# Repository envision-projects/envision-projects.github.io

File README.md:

# [envision-projects.github.io](https://envision-projects.github.io)
Project and certification website for the EnVision makerspace, for use by EnVision administration

## Content Management System

This is the quickest and simplest option for writing and setting up a page. Navigate to [envision-projects.github.io/admin](https://envision-projects.github.io/admin) and sign in with your GitHub account. If prompted, you must give Netlify CMS permission to author commits and push on your behalf. 

After signing in, you can access the different sections of the website and view media that has been uploaded. The CMS is pretty self explanatory.

- Everything is organized into pre-defined sections; there is unfortunately not _yet_ support for nested folders. 
- Files titled `_index.md` are top level files; for example, when you click on **Mechanical** on the website, it takes you to the `_index.md` file for the mechanical section. 
- In the editor, you can either edit in WYSIWYG _"Rich Text"_ mode, or you can edit the markdown directly. 
- The preview on the right gives a basic preview of how the website will look.
- In the rich text editor, you can add links, headings, quotes, code blocks, and other elements (found under the `+` tab.)
  - For images, use the `image` element and please upload your image to the website by clicking `choose an image > upload`
  - `Tip` and `Warning` elements make your article more readable and highlight important information
  - When creating a link, use either the absolute location of the page or the relative location. For example, to link to `envision-projects.github.io/mechanical/3d-printing` the text of my link would read `/mechanical/3d-printing`. Otherwise, `3d-printing` if the file I was editing was in the same folder as the the file I was linking

When editing the page is complete, make sure that you have a title and a description (the publish date may be left as is, or set to the current time by clicking `now`). This will author a git commit with your changes and start the process of the page getting published, which should take around 5 minutes or so.

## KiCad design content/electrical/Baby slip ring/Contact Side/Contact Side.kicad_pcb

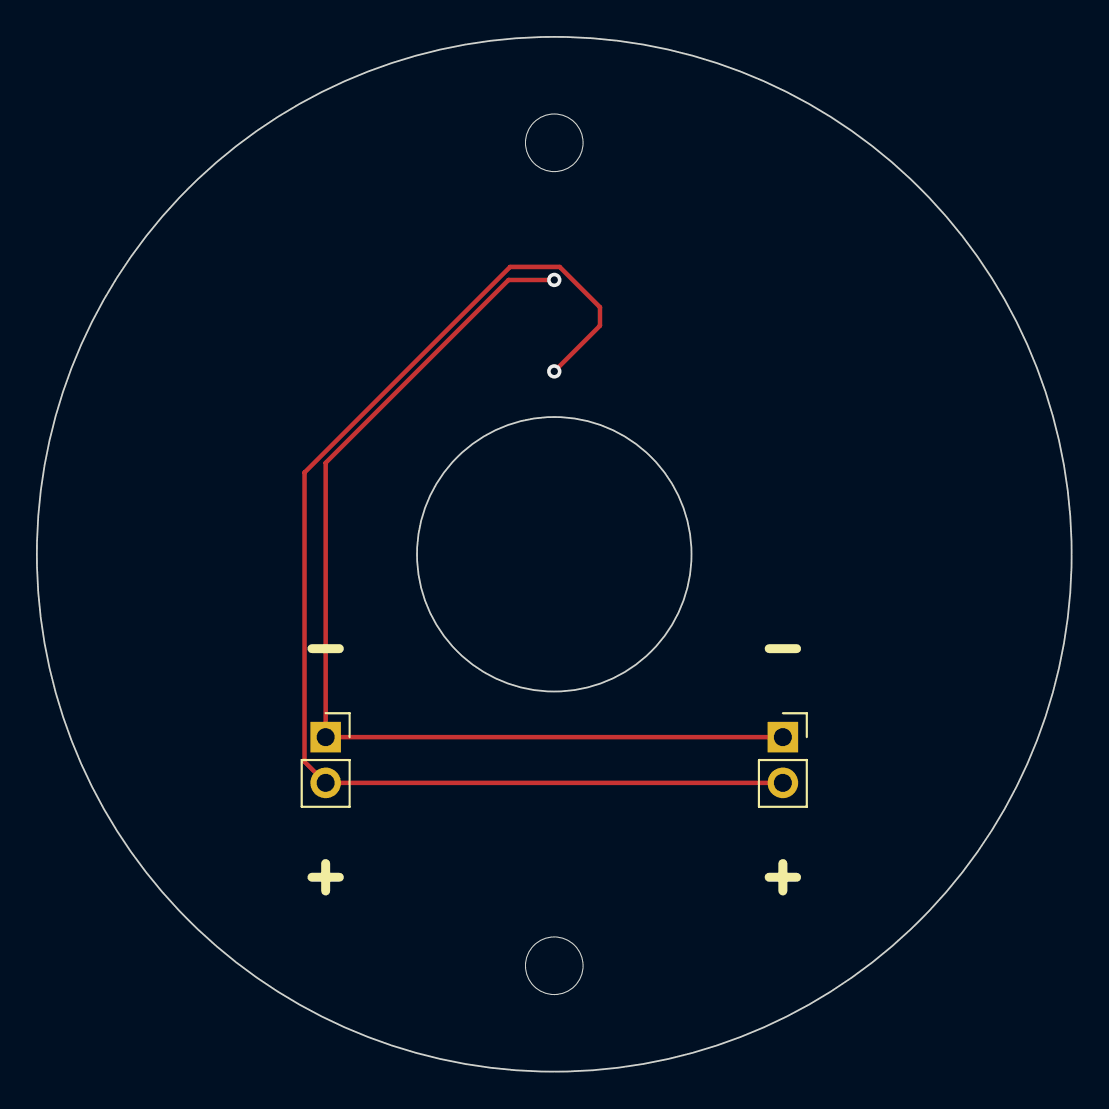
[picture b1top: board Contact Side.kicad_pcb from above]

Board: 2 copper layers, 57.5 x 57.5 mm, 3 parts (0 on the bottom side), 2 nets.

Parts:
D1, D2: LED; PinSocket_1x02_P2.54mm_Vertical
U1: 2_Wire_contact; Contact Pads

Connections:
unnamed: D1.1 (K), D2.1 (K), U1.2 (GND)
unnamed: D1.2 (A), D2.2 (A), U1.1 (+)

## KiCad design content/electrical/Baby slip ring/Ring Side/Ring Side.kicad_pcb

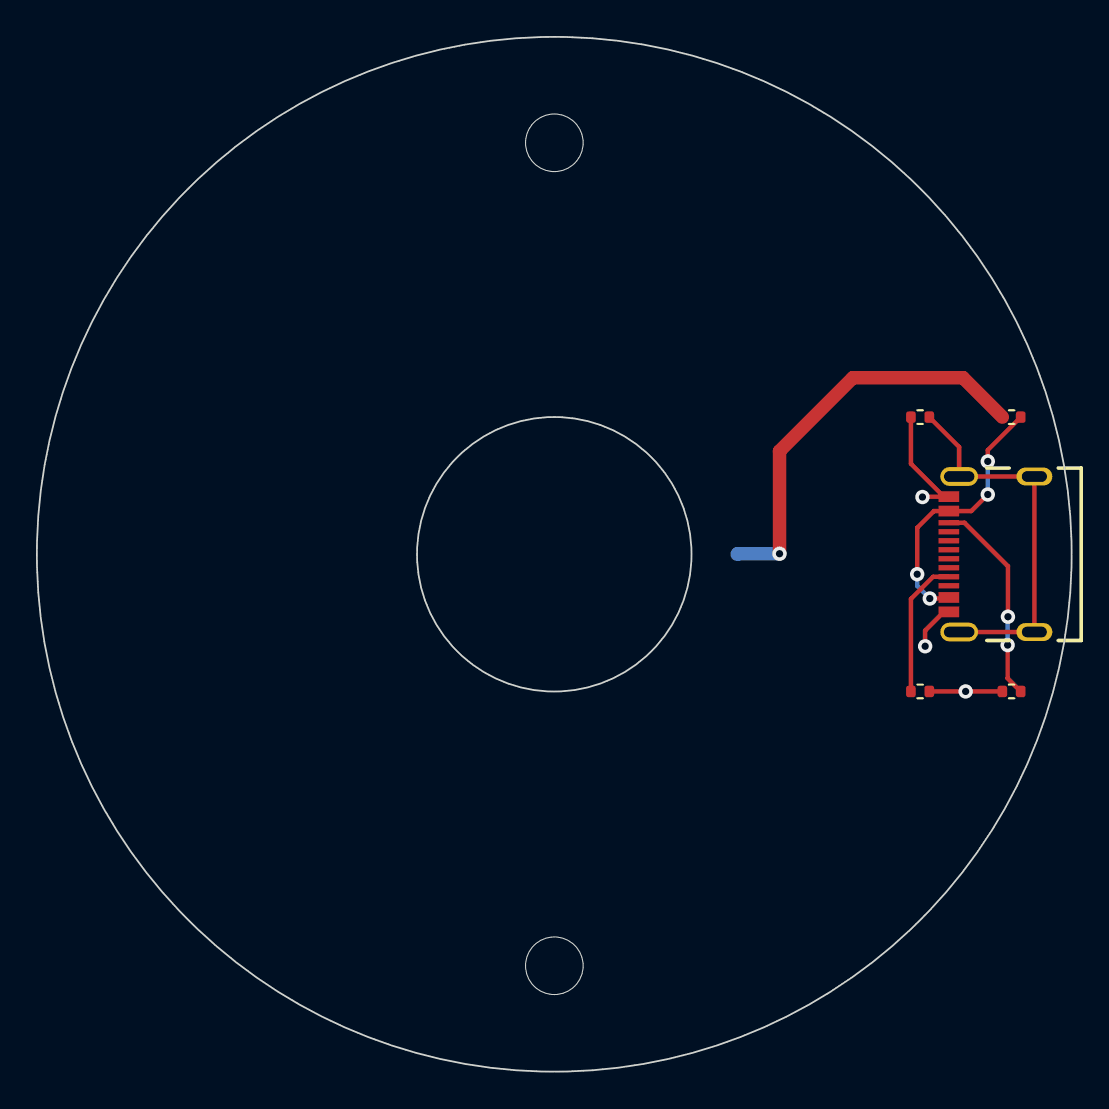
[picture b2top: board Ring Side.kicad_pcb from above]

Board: 2 copper layers, 57.5 x 57.5 mm, 6 parts (0 on the bottom side), 6 nets.

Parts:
J1: USB4105-GF-A; GCT_USB4105-GF-A
R1, R2, R3: 5.1k; R_0402_1005Metric
R4: 470; R_0402_1005Metric
U1: 2_Wire_Ring; 2 Wire Ring

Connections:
GND: J1.A1_B12 (GND), J1.B1_A12 (GND), R1.1, R2.2, R3.2, U1.2 (GND)
unnamed: J1.A5 (CC1), R2.1
unnamed: J1.B5 (CC2), R3.1
unnamed: J1.S1 (SHELL_GND), J1.S2 (SHELL_GND), J1.S3 (SHELL_GND), J1.S4 (SHELL_GND), R1.2
unnamed: R4.1, U1.1 (+)
VCC: J1.A4_B9 (VBUS), J1.B4_A9 (VBUS), R4.2

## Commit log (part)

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2022-08-20 Upload “static/images/ss_arduino3.png”
2022-08-20 Upload “static/images/ss_arduino4.png”
2022-08-20 deploy: 2372934986aabecab25a083c6f30b87d16d41531
2022-08-20 deploy: ffc908f2f898e9946a42e9ee863fea94732f23bf
2022-08-20 Update Embedded Doc “simplesynth-project”
2022-08-20 deploy: 133ec2f00fa13bb67a5334d09d234f5a2b53127c
2022-08-20 deploy: 40410a8e25bdb81d0f237bd15896728e04bf8dff
2022-08-20 deploy: 8ceef5e628713276af94d59dcca4fada12961cde
2022-08-20 deploy: 50fd72f3267697be6b3bff215566b59305df6ea2
2022-08-20 deploy: 155d112f24f32613291aa5aaef3b2dea806dec3c
2022-08-20 Upload “static/images/ss_arduino5.png”
2022-08-20 deploy: 29a4fec32ebb02036e70014a1d3cc810db219dc3
2022-08-21 deploy: b7fe7fb9bde3a6ba3234f25e762e081013418df0
2022-08-21 deploy: 04b6dcef45a325cac162a2d89fcd979c88191e97
2022-08-21 deploy: 1d4640db6f8ef7461e3dbfcc6b8ed846a95634ac
2022-08-21 deploy: 3e80fe1010d79a2bc296ffe44b24c91c7f3f80b6
2022-08-21 Upload “static/images/ss_arduino6.png”
2022-08-21 deploy: e3aaaaf135ae04b4449748d5dd0e17e8b8a83cf4
2022-08-21 deploy: ea1c58187608d7010fc90b4f36d01908c555f3cf
2022-08-21 deploy: e2c86d121907457488cf06fd51179e16c65fa246
2022-08-21 Upload “static/images/ss_arduino7.png”
2022-08-21 Upload “static/images/ss_arduino8.png”
2022-08-21 Upload “static/images/ss_arduino9.png”
2022-08-21 deploy: 536dd113ab888d18e6fb7fc49f578e0ecc064b4a
2022-08-21 deploy: ddb818c62ab50bc87a0f1c0744fa16b6ff034ac3
2022-08-21 deploy: 63f21a9aa49874f6ecfaf76b174b1cf13b130a9e
2022-08-21 deploy: 64e6962d8ffcb7b05a55ab547d92bc5ad229678c
2022-08-21 deploy: 253067c8290102d94707a06eb677e59a7d906e8b
2022-08-21 deploy: fb1c90918f9881cf0ca3361f134dafda739fe788
2022-08-21 Upload “static/images/ss_asd7.png”
2022-08-21 Upload “static/images/ss_asd4.png”
2022-08-21 Upload “static/images/ss_asd5.png”
2022-08-21 deploy: e3cb9491196d23922fbf4fa6283915c229c482e1
2022-08-23 Update Electrical Doc “_index”
2022-08-23 deploy: 5b276313f6897d91253888ef9ddf6fb67e22ab25
2022-08-29 Create Embedded Doc “simple-wifi-web-server-with-esp32”
2022-08-29 deploy: 7a8b777f4c6e641a7c80bcceb4767f4bca2049fa
2022-08-29 Update Mechanical Doc “obstacle-avoidance-robot”
2022-08-29 deploy: 35ebc5b0f1e6f5763af90d114c35b2404856c3d9
2022-08-30 Create Mechanical Doc “project-l0ckcr4ck3r”
2022-08-30 deploy: 37055d325373964d2c4641ce070369deffb1a842
2022-08-30 Update Mechanical Doc “project-l0ckcr4ck3r”
2022-08-30 deploy: f9e002000a29d2e881472fa5f6bd84323a2a0fe1
2022-08-30 deploy: ff04cbd709252626fddf5c37c6f145cd3c9cbd27
2022-08-30 deploy: 7b3a587575719f9b86e02f8b72a5f88a05d18b2c
2022-08-30 deploy: ea52a347ff7f4f624bd7126236e9bb61020f5812
2022-08-30 deploy: d7cf5d3192198a8254e8a4a2e8539a88462bb509
2022-08-30 deploy: 09c6ae3f73d2ba72500f98a9014e268b1935a6d0
2022-08-31 Update Embedded Doc “simple-wifi-web-server-with-esp32”
2022-08-31 deploy: 750403e3f271476c4f5d2160757f8f60e879f4d7
2022-08-31 deploy: ab5501759b2f79258ad91544b069bda1cb30e672
2022-08-31 deploy: 486b5b6fa540669623f064c1f1d3f2e32045e59e
2022-08-31 deploy: f022e614af71349da2cb04f02d0964e4b0ddcd81
2022-08-31 deploy: 02147ab66fbd1c33d2828dca0936b0f8c805107b
2022-08-31 deploy: 4652c6294a9de4e34150ec6c163e45cb45c947d9
2022-09-01 deploy: f131f90a6e9c699339910415a3e7dbcc55f09c0e
2022-09-01 deploy: 407a009b6af61ad27f21a4f1174adfa432f88623
2022-09-01 deploy: d9e0f49a03fcde041c96fa9292fbe3138cb65878
2022-09-01 deploy: 4816ac3cbb18455e172e83b95272ff5fcaba6f70
2022-09-01 deploy: f6cb04aca606c8b09c98121dd9aea54c76859f15
2022-09-01 deploy: 1274ad97bbf1538e5c3371144fbfb34e67c90cd5
2022-09-01 deploy: 8dfc9406b921060639452addb7e6526e5b9cb090
2022-09-01 deploy: a373006af7bc060fb5bb53ad394478b9b9963707
2022-09-01 deploy: 5abb88158a2e0346899f5e6f462bead844b75a7d
2022-09-01 deploy: 3a3bfb0c38af4fb283da7f818c3b8a033f6747b6
2022-09-01 deploy: f7052a893f02fe28706d8360e6621192329b3825
2022-09-01 deploy: 9ff7b30d6d923994806feb3c80151ca2ea49b99d
2022-09-01 deploy: bf124ceaf0b6ba651b0ab3edc3311bd49cb57fc1
2022-09-02 deploy: 99028bb35a3ca4553b590265de661ba5d076d499
2022-09-03 deploy: 0b51792fbed1a314f044ad5a755999a91d32e878
2022-09-06 Create Embedded Doc “blynk-wifi-tutorial”
2022-09-06 deploy: 9ea47b03fe48d2496921b56e431b548d7542ef4c
2022-09-06 Update Embedded Doc “blynk-wifi-tutorial”
2022-09-06 deploy: e2c7eecd42ed6c8f09b66e97ff57fe9fa9e5b20b
2022-09-07 deploy: 81ac32fac64a584271c174b6c32929162dd21378
2022-09-07 deploy: fe3f250e30f83c96be3de6b10261d23322e0135c
2022-09-07 deploy: 60656cd6bb1d14a111363d8d0c11d6ae4dcf9581
2022-09-07 deploy: 993a4b892a4922138aa70b6484e7d3697cab1373
2022-09-07 deploy: 5556a275407f125540cdf6ed72b8d5dd06316f5a
2022-09-07 Create Embedded Doc “led-audio-sound-level-display-vu-meter-analyzer”
2022-09-07 deploy: 1653b1c89102ee8b248edbe0a86ae8e23cdbca39
2022-09-07 Update Embedded Doc “led-audio-sound-level-display-vu-meter-analyzer”
2022-09-07 deploy: e5427ba3410c5c9ad5d3c9f856e210d6e914eb53
2022-09-07 deploy: b13b9ebcabd17c084cc0de7b4e9db1c1661ea640
2022-09-07 deploy: e57d99d8ff60a0e90f47cc7446408313dce61303
2022-09-08 deploy: b5724c0e1ce71e92477758de7d29ed42f7615e94
2022-09-08 Upload “static/images/muxnets.png”
2022-09-08 deploy: 34a64aca175f7eaf1dfb76178ddc291148b8c51a
2022-09-08 deploy: 60998dd3fa49b766cf202867a81a1f9693ce0cf4
2022-09-08 deploy: 34e02fc4e6b3e83764e7942d42dc24004c9cbe65
2022-09-08 deploy: df14c856cb01af8944d3d222f5ab7132a02dd300
2022-09-08 Upload “static/images/ss_schematic3.png”
2022-09-08 deploy: c185b58855e568ab4e39f24bd72bbbfd259c44fe
2022-09-08 deploy: 11a450586ce1e5ef953f33afd7590d88e395bca1
2022-09-08 deploy: 082cf41aa2129a48c9f4a88f73624b0c497e2220
2022-09-08 deploy: d0abd1523ed1c82c6f4da519db33169f5850094b
2022-09-09 deploy: 85ca82b3ee60feccca57ca88ffcf34fa55a02056
2022-09-09 deploy: 028c70381e6c202687dbdc20ae346cadf58f71da
2022-09-09 deploy: 98bed813e22c8db5454f47e5985da2e99ce460cc
2022-09-10 deploy: d03ad68e18bfc704c50d2b872bf38215e392580b
2022-09-11 deploy: f40c3957ca615ea6060f1572d081d8ccf9a89759
2022-09-11 deploy: b297718731fc83b98b909fb7aa782b757230391a
2022-09-11 deploy: a32e0a05685458ab42a371abb00b05ded6a58fb4
2022-09-11 deploy: 778cc724083931255905fd9e183d0cd1e2e61f4c
2022-09-11 deploy: ed745ddbcde84cbe031fac15a125fc1e509ff32d
2022-09-11 deploy: 13149669bcf0ca276e82eaae39dd8245e0570a79
2022-09-11 deploy: ff0462dd52d15f1f735a9fb95c1e1da68d3b513b
2022-09-12 deploy: e275f171ee4c8e0d3c6fc3597c212b2d5e14ff8c
2022-09-12 deploy: e0f286e646667c9542d69743b793c3d21c5b2152
2022-09-12 deploy: e46f7c6750a91f31199e87ca017a65c025a9950b
2022-09-12 deploy: 4bf16bb42dd1f16d2e4807824f4266222c81296a
2022-09-13 Update Embedded Doc “_index”
2022-09-13 deploy: f38d904c3aae0e1fb5e608c11cc6f14e17d9da1c
2022-09-13 deploy: a8a227c87ed60fbf086c980373757d611944ac9a
2022-09-13 deploy: ec4550f1e163ab8c6adf9a3b5015a04703e11d3a
2022-09-13 deploy: b3910de9b33a95a9fc41b2751b40b2c79db2610c
2022-09-14 deploy: c44c421a132470cac24176898574cb68a02612f8
2022-09-14 deploy: 9d29c187d6108e68b1892dbc6d02645d28db51e1
2022-09-14 deploy: f194ee674eed02ee1fe21c5fdab830ad7d2dcd16
2022-09-14 deploy: 533e5769da5851fc2d07b190be3bea73c4821f17
2022-09-14 deploy: 073531a403b6b36fca712901afc18d0535396220
2022-09-14 deploy: a6d4a1d7e4efc165e3c77ceeca7daa7aa019046d
2022-09-14 deploy: 56562c23ed48640e59958ad0983c8a74b06cf076
2022-09-14 deploy: 457b77590d107b5955c959c9e69ae8936716c929
2022-09-15 deploy: a861e079e02746f9e1859140903731471be72289
2022-09-15 deploy: 2cb31226fa2988e9a8e8846a74b95c1dfe7f978d
2022-09-15 deploy: 7e4b67c662bbcd2e62f7f21f769f008f3b3a4542
2022-09-16 Update Mechanical Doc “_index”
2022-09-16 deploy: 9e80b807f01d3de444c7c186aac7509a5ff39e19
2022-09-16 Update Tutorial “_index”
2022-09-16 deploy: f1f24b6c9de018904fb927beb1830a4c927da6ba
2022-09-16 deploy: b350f58df76a4796a3a93af041365e244913a87a
2022-09-16 deploy: 49013bd1da9cc49bc78f2c7929dffead12ddddfe
2022-09-16 Update Electrical Doc “familiarize-yourself”
2022-09-16 deploy: 5be6904cb5ec4ffcf4715fcdd9a9491b78475959
2022-09-16 deploy: 49bf6979023b104f9b65dd425cfa200b8b9e781c
2022-09-16 deploy: b1a01d5b6e9e486f95354ffdbc20004222885faf
2022-09-16 deploy: c40e896cf9afc75f88b1e6e0b07228b59d22bdb5
2022-09-16 deploy: 8542aa06f485f842ee5af633038a241f0dc51c61
2022-09-16 deploy: a13a47d6b1f0273637c8c2e697d2332bf2e40780
2022-09-16 deploy: 09533a0afe26e3d329501af4150eb1bdb1d0f2f1
2022-09-16 Create Tutorial “exporting-gerbers-altium”
2022-09-16 deploy: 52dc269c85eb5b4dbc30d0365d243f08143ef219
2022-09-16 deploy: be9f9c7ddd2f30c50e208f532a1006e88994cb74
2022-09-16 deploy: 789cb6d640d0e2063b2413a1db5be3ed1a73a30b
2022-09-16 Create Tutorial “pcb-layout”
2022-09-16 deploy: a9294d7b14b064900824514628f3b9e4f62e7c42
2022-09-16 Create Tutorial “schematic-design”
2022-09-16 deploy: 7bab014c015f52de76d34c3e2ecdd1abbb5a7abc
2022-09-16 Update Electrical Doc “pcb-layout”
2022-09-16 Update Electrical Doc “schematic-design”
2022-09-16 deploy: 5a5e27a4975773db3b219f4b4357791f95cdc3e5
2022-09-16 deploy: 85753a3ca59524e0c9cdbc4460af1b8c36337f25
2022-09-16 deploy: ecd63694014232d49ae4222f8c0e471f5f4183de
2022-09-16 Update Mechanical Doc “walking-robot”
2022-09-16 deploy: c9f29e8115ba7dd94659c7025661779450723a5b
2022-09-16 deploy: 70f3b6313f9f759f376298b16edd1af67eda0a6f
2022-09-16 deploy: fadec17af79904b7fa32775add28a4381a21a0ce
2022-09-16 deploy: 19d797ee91233a95d8b59d8427fdaba1f9da4373
2022-09-16 deploy: 55cc3afa9913cef8f5370d2ba96e8aae70dc79ac
2022-09-16 deploy: 489601d734883ad4c4aa77b1b9112a46d2853ce3
2022-09-19 Create Mechanical Doc “automatic-out-the-front-comb”
2022-09-19 deploy: 2d986c2db39a76cc259a109b03fe61a06e5ff382
2022-09-22 Fix README Link
2022-09-22 moved around tutorial pages
2022-09-22 deploy: 7288f02468b9cc5290d95e21d5b808dc4a00f48b
2022-10-06 Create Mechanical Doc “double-action-out-the-front-comb”
2022-10-06 deploy: cb144423bc4c73cb1a6172864948df9a3004e7bc
2022-10-06 Update Mechanical Doc “double-action-out-the-front-comb”
2022-10-06 deploy: 45881159be05624ff6d23fc6711401a551b52079
2022-10-06 deploy: df20378b346ac5e43f509cab29bc50d92146f306
2022-10-06 deploy: 63d75229fa6614e48f1b68424b26c1799d9d719b
2022-10-14 deploy: 99d982620a6d2c61144ab2481d8b9807729beec7
2022-10-14 deploy: e22804cdd1f22171f65ce05e2982977fa7fd24da
2022-10-14 deploy: bb42049ec4caebdb4fe0e758eff2dd178e003594
2022-10-29 Create Tutorial “96-oled-screen”
2022-10-29 deploy: f97fe13959059302a13aad4f647c139f3a521aef
2022-11-05 deploy: 18949e0ecdd45aa2818e116466dc4a3d04c56242
2022-11-05 deploy: 32b57991398c636a0e1d29ff2f9b16c9a9da6413
2022-12-21 deploy: 2295f7b7012435f90439e8c7cc6d4d05232fcb09
2022-12-28 deploy: 0863606ed5cb93bfe62f36cad878b5bfda443829
2023-01-05 deploy: 6d87e45265023bc4f488a746355bb03c14ed5617
2023-01-05 deploy: 4393b9fc5e37e62163e705c4653d9bacd7094465
2023-01-05 deploy: bcb43151389acd3f4b379506773e1e1f0e05b600
2023-01-05 deploy: 0f06ca15e600569d77cd4bc96f34bb830668ee12
2023-01-05 deploy: def019563eb240a4f9a9bef5569ca9c14c5f3b4d
2023-01-05 deploy: fdc0f3a00d6de6673106c44702bbc5289381da1e
2023-01-05 deploy: b2eab0b3b693a7c366b78c5d2c3f1cbbd8167f0f
2023-01-26 deploy: 855b58e4dfc942c61bd4d0889e5c8f9269d7627b
2023-02-01 deploy: 604d6a5a75ce734a96b97a05e649375d2441d873
2023-04-26 Create Embedded Doc “test”
2023-04-26 Update Embedded Doc “test”
2023-05-10 deploy: 24855eef26db2a8f110134f6d25008dd3cb73d4e
2023-05-10 deploy: a0a9408de595e7fa20f599254897772147b20316
2023-05-22 Upload “static/images/simplesynth2.jpg”
2023-05-22 Upload “static/images/simplesynth3.jpg”
2023-05-22 deploy: 58f18e141aa4fb1e40cfab6aa073123b3963ab35
2023-05-22 deploy: 00345ac8a4240a4250961eefc846d6f36f756106
2023-05-22 deploy: afdbb7ed49a2409651e083472df1ebaeb7b8b655
2023-05-22 deploy: e1b8eff8b2496f19c0aa24d70feac4416e752a9c
2023-05-26 deploy: db5e22bb9554412a4712814f15f4d1d0188d2dec
2023-05-26 deploy: 0e3a580792d6435fd5ff4b6bac341d3c000321fd
2023-05-26 deploy: 9f5631c45410dc4f877f49cd3e6cf15b3c306aee
2023-06-16 deploy: 8125644f545de780474d68b649f274ff6de8537e
2023-06-16 deploy: 1833c6458ec37fd81f9829573a5696ffb70a6343
2023-06-16 deploy: 4edb0332aa24750f2f4e022bec617ec088852b56
2023-06-19 deploy: 7dd6d0ffcde5ddbdc8d021f293d96d43d1298fb7
2023-06-19 deploy: d5706b0710cb3f5fa47e17e4a52685da0e2aca0c
2023-06-22 deploy: 196906665b114e2f5c33cd3f0411c18b002a6082
